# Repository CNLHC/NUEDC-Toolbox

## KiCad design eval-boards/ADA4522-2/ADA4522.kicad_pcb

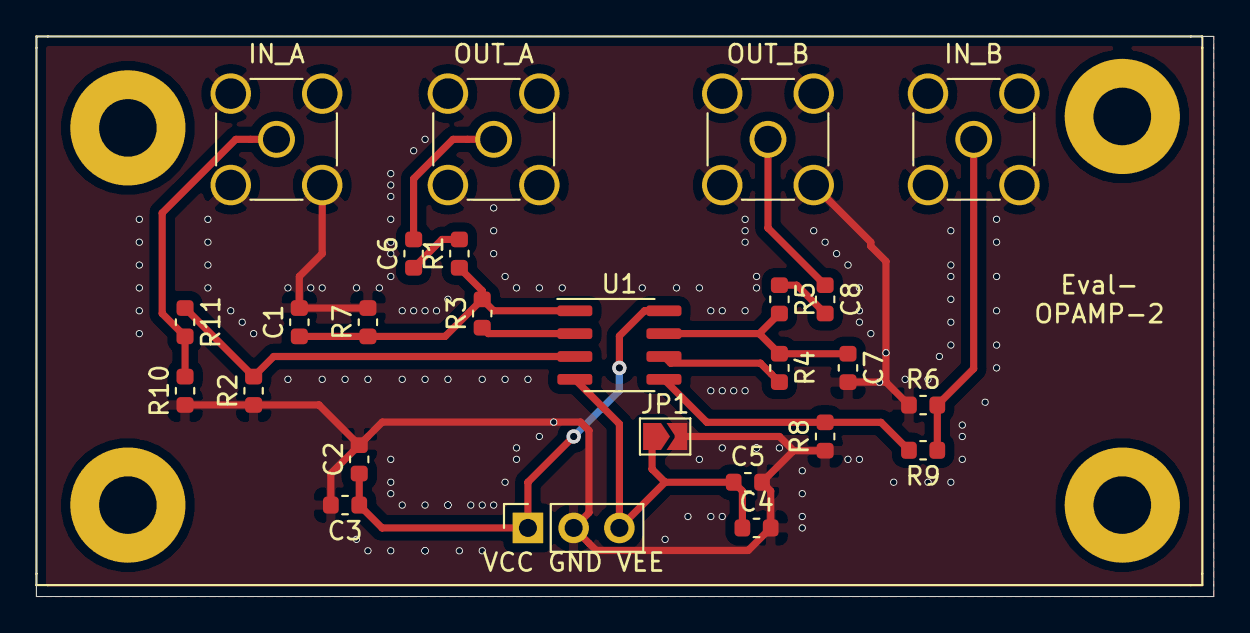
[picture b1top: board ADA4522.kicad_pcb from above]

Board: 2 copper layers, 65.4 x 31.1 mm, 26 parts (0 on the bottom side), 15 nets.

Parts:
C1, C6, C7, C8: 100pF; C_0603_1608Metric
C2, C4: 10uf; C_0603_1608Metric
C3, C5: 0.1uf; C_0603_1608Metric
IN_A: IN_A; SMA_Amphenol_132134-11_Vertical
IN_B: IN_B; SMA_Amphenol_132134-11_Vertical
JP1: SolderJumper-2_P1.3mm_Open_TrianglePad1.0x1.5mm
OUT_A: OUT_A; SMA_Amphenol_132134-11_Vertical
OUT_B: OUT_B; SMA_Amphenol_132134-11_Vertical
R1, R2, R3, R4, R5, R6, R7, R8, R9, R10, R11: R; R_0603_1608Metric
U1: ADA4522-2; SOIC-8_3.9x4.9mm_P1.27mm
VCC GND VEE: Conn_01x03_Male; PinSocket_1x03_P2.54mm_Vertical

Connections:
GND: C1.2, C2.2, C3.2, C4.2, C5.2, C7.2, IN_A.2, IN_B.2, JP1.2, OUT_A.2, OUT_B.2, R2.1, R6.1, R7.2, R8.1, R10.1, VCC GND VEE.2
unnamed: C1.1, R1.1, R3.2, R7.1, U1.1
unnamed: C2.1, C3.1, U1.8, VCC GND VEE.1
unnamed: C4.1, C5.1, JP1.1, U1.4, VCC GND VEE.3
unnamed: C6.1, R1.2
unnamed: C6.2, OUT_A.1
unnamed: C7.1, R4.1, R5.2, U1.7
unnamed: C8.1, OUT_B.1
unnamed: C8.2, R5.1
unnamed: IN_A.1, R10.2, R11.2
unnamed: IN_B.1, R6.2, R9.1
unnamed: R3.1, U1.2
unnamed: R4.2, U1.6
unnamed: R8.2, R9.2, U1.5
unnamed: R2.2, R11.1, U1.3

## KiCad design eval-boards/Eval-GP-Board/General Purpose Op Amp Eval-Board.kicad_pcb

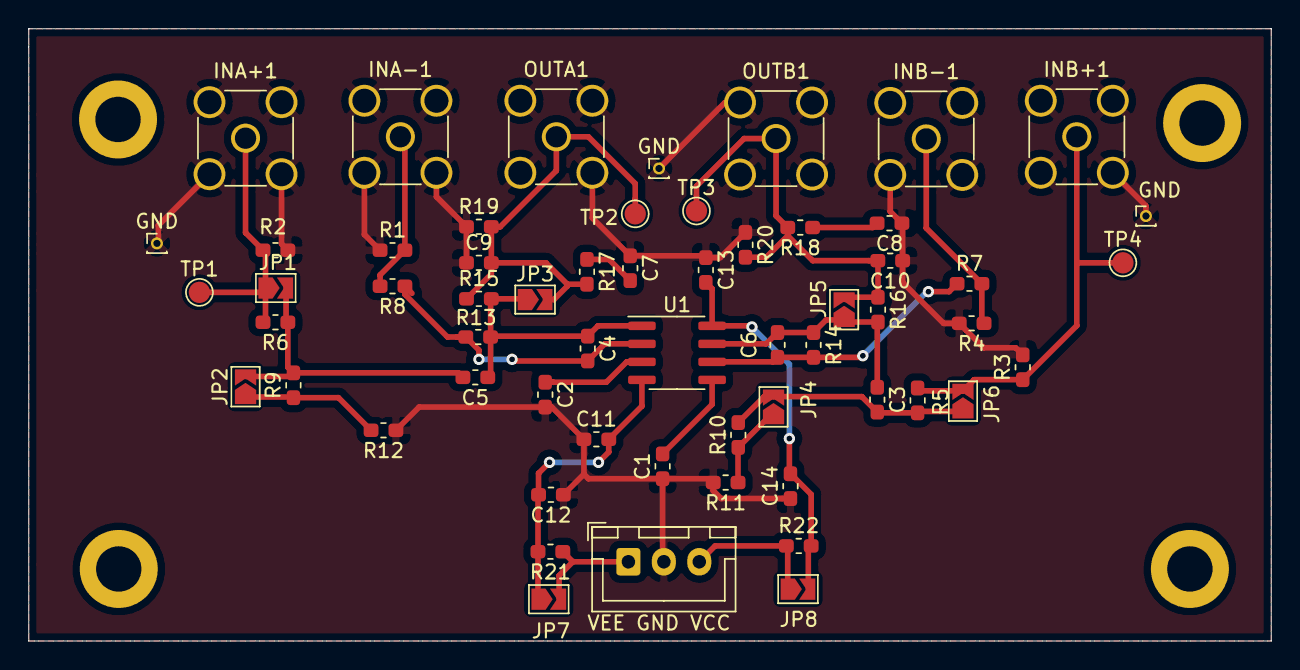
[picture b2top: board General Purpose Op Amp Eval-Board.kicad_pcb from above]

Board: 2 copper layers, 87.6 x 43.2 mm, 59 parts (0 on the bottom side), 23 nets.

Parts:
C1, C2, C3, C4, C5, C6, C7, C8, C9, C10, C11, C12, C13, C14: C; C_0603_1608Metric_Pad1.05x0.95mm_HandSolder
GND: PinHeader_1x01_P1.00mm_Vertical
GND#2, GND#3: PinHeader_1x01_P1.00mm_Vertical
INA+1: Conn_Coaxial; SMA_Amphenol_132134-11_Vertical
INA-1: Conn_Coaxial; SMA_Amphenol_132134-11_Vertical
INB+1: Conn_Coaxial; SMA_Amphenol_132134-11_Vertical
INB-1: Conn_Coaxial; SMA_Amphenol_132134-11_Vertical
JP1, JP2, JP3, JP4, JP5, JP6, JP7, JP8: SolderJumper-2_P1.3mm_Open_TrianglePad1.0x1.5mm
OUTA1: Conn_Coaxial; SMA_Amphenol_132134-11_Vertical
OUTB1: Conn_Coaxial; SMA_Amphenol_132134-11_Vertical
R1, R2, R3, R4, R5, R6, R7, R8, R9, R10, R11, R12, R13, R14, R15, R16, R17, R18, R19, R20, R21, R22: R; R_0603_1608Metric_Pad1.05x0.95mm_HandSolder
TP1, TP2, TP3, TP4: TestPoint_Pad_D1.5mm
U1: ADA4075-2; SOIC-8_3.9x4.9mm_P1.27mm
VEE GND VCC: Conn_01x03_Male; JST_XH_B3B-XH-A_1x03_P2.50mm_Vertical

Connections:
/VCC: JP8.1, R22.1, VEE GND VCC.3
/VEE: JP7.2, R21.1, VEE GND VCC.1
GND: C1.1, C2.2, C7.1, C8.1, C9.1, C10.1, C11.1, C12.1, C13.1, C14.1, GND.1, GND#2.1, GND#3.1, INA+1.2, INA-1.2, INB+1.2, INB-1.2, OUTA1.2, OUTB1.2, R1.1, R2.1, R3.2, R4.2, R11.2, R12.1, R19.1, R20.1, VEE GND VCC.2
unnamed: C1.2, U1.5
unnamed: C2.1, U1.3
unnamed: C3.1, C6.1, JP5.1, R14.1, R16.2, U1.7
unnamed: C3.2, JP4.2, JP6.1, R5.1, R10.2
unnamed: C4.1, C5.1, JP3.1, R13.1, R15.2, U1.1
unnamed: C4.2, R8.1, R13.2, U1.2
unnamed: C5.2, JP1.2, JP2.2, R6.1, R9.2
unnamed: C6.2, R7.1, R14.2, U1.6
unnamed: C7.2, R17.1
unnamed: C8.2, R18.1
unnamed: C9.2, JP3.2, OUTA1.1, R15.1, R17.2, R19.2, TP2.1
unnamed: C10.2, JP5.2, OUTB1.1, R16.1, R18.2, R20.2, TP3.1
unnamed: C11.2, C12.2, JP7.1, R21.2, U1.4
unnamed: C13.2, C14.2, JP8.2, R22.2, U1.8
unnamed: INA+1.1, JP1.1, R2.2, R6.2, TP1.1
unnamed: INA-1.1, R1.2, R8.2
unnamed: INB+1.1, JP6.2, R3.1, R5.2, TP4.1
unnamed: INB-1.1, R4.1, R7.2
unnamed: JP4.1, R10.1, R11.1
unnamed: JP2.1, R9.1, R12.2

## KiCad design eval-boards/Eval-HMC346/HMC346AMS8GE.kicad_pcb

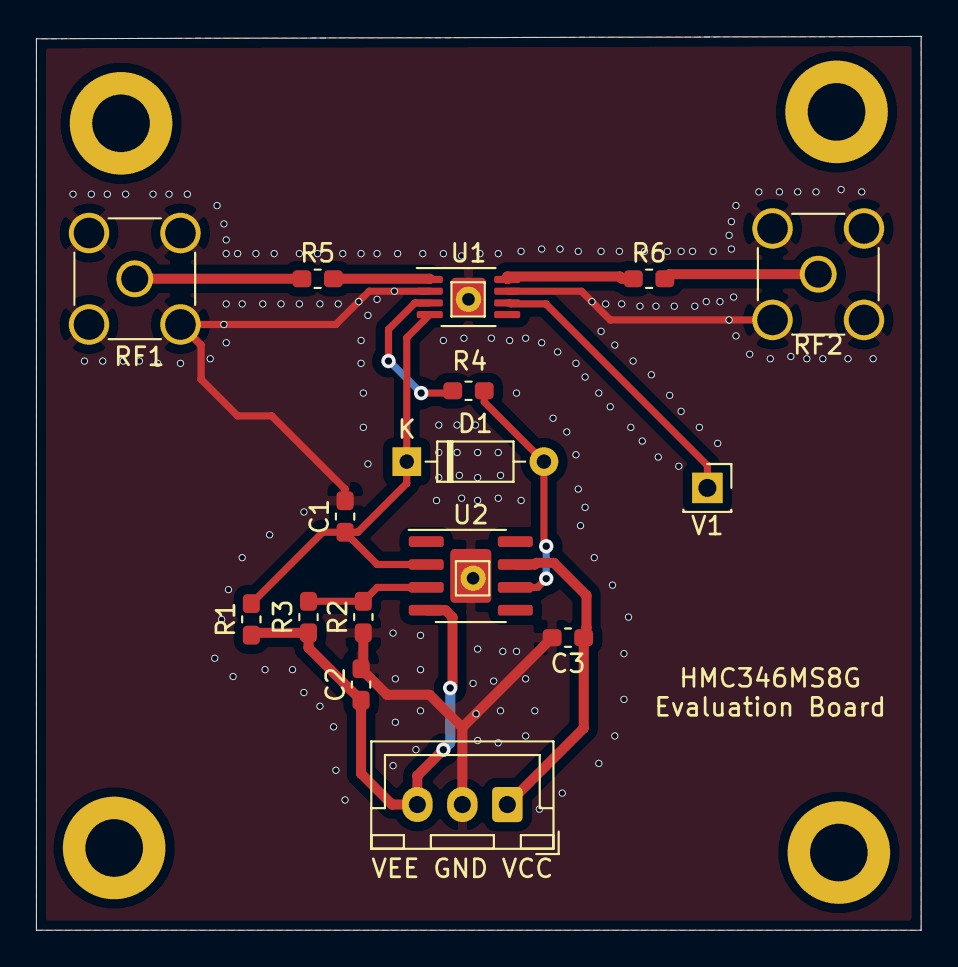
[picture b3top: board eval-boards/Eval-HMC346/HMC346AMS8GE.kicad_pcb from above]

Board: 2 copper layers, 49.1 x 49.7 mm, 16 parts (0 on the bottom side), 12 nets.

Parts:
C1, C2, C3: C; C_0603_1608Metric_Pad1.05x0.95mm_HandSolder
D1: 1N4148; D_DO-35_SOD27_P7.62mm_Horizontal
R1, R3: 3.92k; R_0603_1608Metric_Pad1.05x0.95mm_HandSolder
R2: 500; R_0603_1608Metric_Pad1.05x0.95mm_HandSolder
R4, R5, R6: R; R_0603_1608Metric_Pad1.05x0.95mm_HandSolder
RF1, RF2: Conn_Coaxial; SMA_Amphenol_901-144_Vertical
U1: HMC346AMS8GE; MSOP-8-1EP_3x3mm_P0.65mm_EP1.95x2.15mm
U2: THS4631D; SOIC-8-1EP_3.9x4.9mm_P1.27mm_EP2.29x3mm
V1: Conn_01x01_Male; PinSocket_1x01_P2.54mm_Vertical
VEE GND VCC: Conn_01x03_Male; JST_XH_B3B-XH-A_1x03_P2.50mm_Vertical

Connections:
/I: C1.1, D1.1, R1.2, U1.4, U2.2
/V1: U1.6, V1.1
/V2: R4.2, U1.3
/VCC: C3.1, U2.7, VEE GND VCC.1
/VEE: C2.1, R1.1, R3.1, U2.4, VEE GND VCC.3
GND: C1.2, C2.2, C3.2, R2.1, RF1.2, RF2.2, U1.2, U1.7, U1.9, U2.9, VEE GND VCC.2
unnamed: D1.2, R4.1, U2.6
unnamed: R5.1, RF1.1
unnamed: R6.2, RF2.1
unnamed: R2.2, R3.2, U2.3
unnamed: R5.2, U1.1
unnamed: R6.1, U1.8

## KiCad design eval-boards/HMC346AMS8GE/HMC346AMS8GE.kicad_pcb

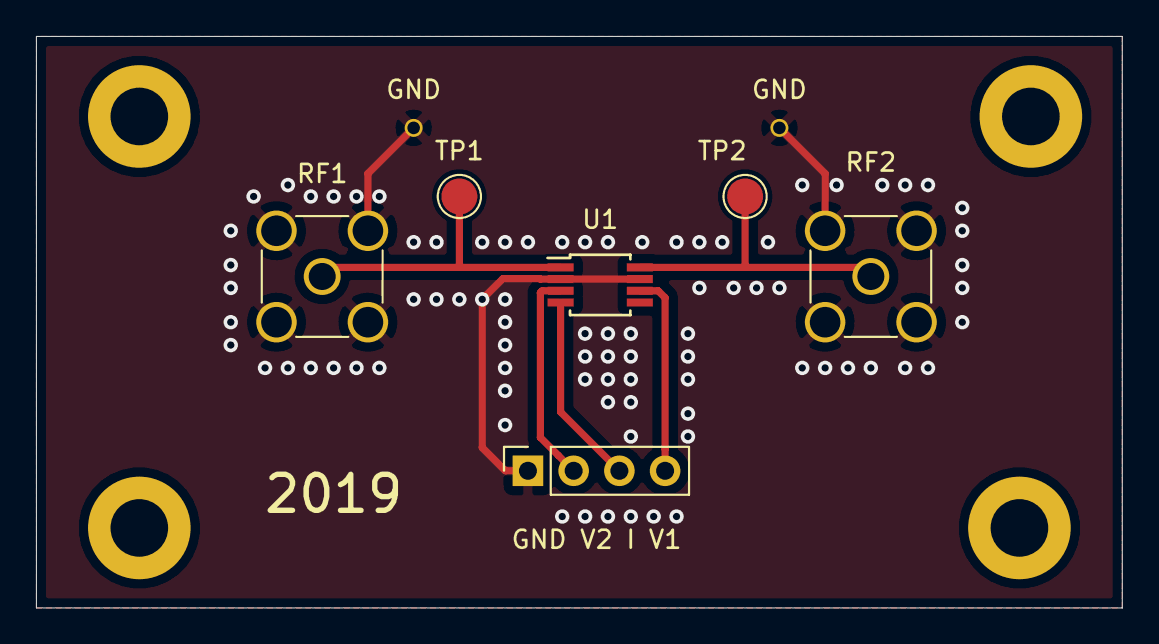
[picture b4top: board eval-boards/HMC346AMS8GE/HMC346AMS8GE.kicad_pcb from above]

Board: 2 copper layers, 60.3 x 31.8 mm, 8 parts (0 on the bottom side), 6 nets.

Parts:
GND: PinSocket_1x01_P1.27mm_Vertical
GND V2 I V1: Conn_01x04_Male; PinSocket_1x04_P2.54mm_Vertical
GND#2: PinSocket_1x01_P1.27mm_Vertical
RF1, RF2: Conn_Coaxial; SMA_Amphenol_901-144_Vertical
TP1, TP2: TestPoint_Pad_D2.0mm
U1: HMC346AMS8GE; MSOP-8_3x3mm_P0.65mm

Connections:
GND: GND.1, GND V2 I V1.1, GND#2.1, RF1.2, RF2.2, U1.2, U1.7
unnamed: RF1.1, TP1.1, U1.1
unnamed: RF2.1, TP2.1, U1.8
unnamed: GND V2 I V1.2, U1.3
unnamed: GND V2 I V1.3, U1.4
unnamed: GND V2 I V1.4, U1.6

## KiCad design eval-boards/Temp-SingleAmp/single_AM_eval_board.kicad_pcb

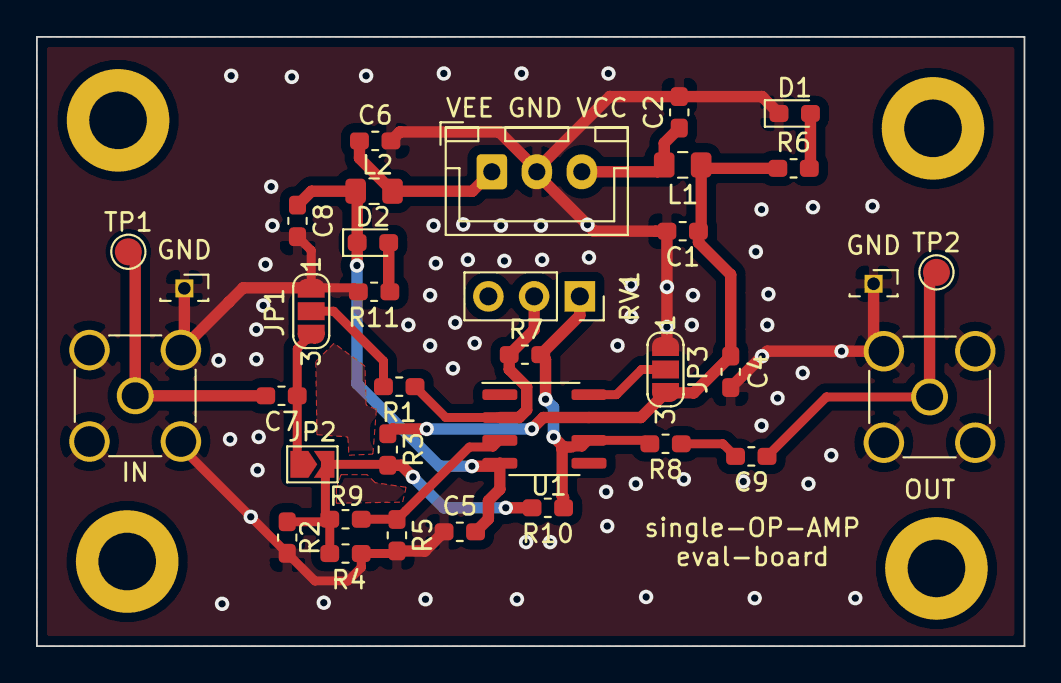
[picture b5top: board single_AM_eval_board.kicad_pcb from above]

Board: 2 copper layers, 54.9 x 33.8 mm, 35 parts (0 on the bottom side), 17 nets.

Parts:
C1, C2, C6, C8: 10uF; C_0603_1608Metric_Pad1.05x0.95mm_HandSolder
C4, C5: 100nF; C_0603_1608Metric_Pad1.05x0.95mm_HandSolder
C7, C9: C; C_0603_1608Metric_Pad1.05x0.95mm_HandSolder
D1, D2: LED_ALT; LED_0603_1608Metric_Pad1.05x0.95mm_HandSolder
GND: PinSocket_1x01_P1.27mm_Vertical
GND#2: PinSocket_1x01_P1.27mm_Vertical
IN: Conn_Coaxial; SMA_Amphenol_132134-11_Vertical
JP1, JP3: Jumper_3_Open; SolderJumper-3_P1.3mm_Open_RoundedPad1.0x1.5mm_NumberLabels
JP2: Jumper_2_Open; SolderJumper-2_P1.3mm_Open_TrianglePad1.0x1.5mm
L1, L2: L_Core_Iron; L_0805_2012Metric_Pad1.15x1.40mm_HandSolder
OUT: Conn_Coaxial; SMA_Amphenol_132134-11_Vertical
R1, R2, R3, R4, R5, R7, R8, R9, R10: R; R_0603_1608Metric_Pad1.05x0.95mm_HandSolder
R6, R11: 1K; R_0603_1608Metric_Pad1.05x0.95mm_HandSolder
RV1: R_POT; PinSocket_1x03_P2.54mm_Vertical
TP1, TP2: TestPoint_Pad_D1.5mm
U1: ADA4522-1; SOIC-8_3.9x4.9mm_P1.27mm
VEE GND VCC: Conn_01x03_Male; JST_XH_B3B-XH-A_1x03_P2.50mm_Vertical

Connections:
/VCC: C1.1, C4.2, JP3.3, L1.1, R3.1, R6.1, U1.7
/VEE: C5.2, C8.1, D2.1, L2.2, U1.4
GND: C1.2, C2.2, C4.1, C5.1, C6.2, C8.2, D1.1, GND.1, GND#2.1, IN.2, JP1.1, JP3.1, OUT.2, R2.2, R4.2, R5.2, R11.2, VEE GND VCC.2
unnamed: C2.1, L1.2, VEE GND VCC.3
unnamed: C6.1, L2.1, VEE GND VCC.1
unnamed: C7.1, JP1.3, JP2.1
unnamed: C7.2, IN.1, TP1.1
unnamed: C9.1, OUT.1, TP2.1
unnamed: C9.2, R8.1
unnamed: D1.2, R6.2
unnamed: D2.2, R11.1
unnamed: JP1.2, R1.2
unnamed: JP2.2, R2.1, R3.2, R4.1, R9.2, R10.2
unnamed: JP3.2, U1.8
unnamed: R1.1, R7.2, RV1.2, U1.2
unnamed: R5.1, R9.1, U1.3
unnamed: R7.1, R8.2, R10.1, RV1.1, U1.6

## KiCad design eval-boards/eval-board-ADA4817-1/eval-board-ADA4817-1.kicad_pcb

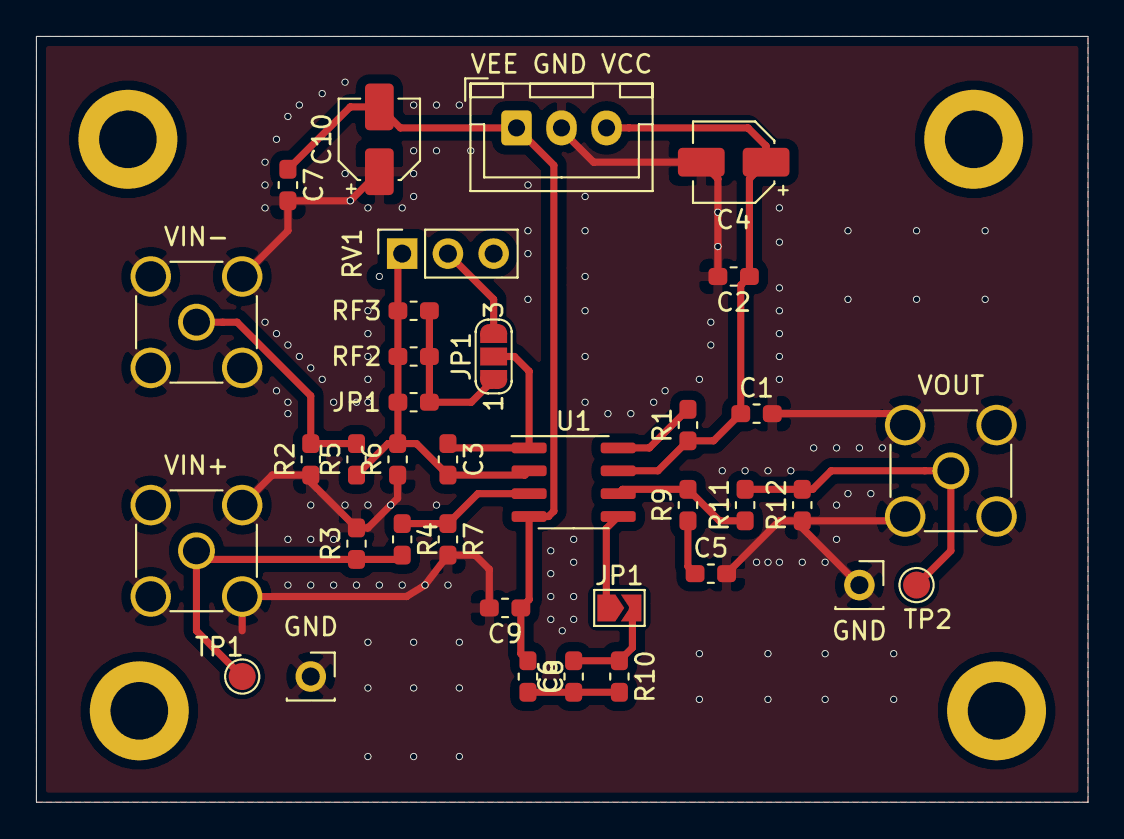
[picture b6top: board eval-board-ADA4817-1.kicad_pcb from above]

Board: 2 copper layers, 58.4 x 42.5 mm, 36 parts (0 on the bottom side), 16 nets.

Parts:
C1, C2, C7, C9: 0.1uF; C_0603_1608Metric_Pad1.05x0.95mm_HandSolder
C3: CF; C_0603_1608Metric_Pad1.05x0.95mm_HandSolder
C4, C10: 10uF; CP_Elec_4x5.4
C5: CL; C_0603_1608Metric_Pad1.05x0.95mm_HandSolder
C6, C8: C; C_0603_1608Metric_Pad1.05x0.95mm_HandSolder
GND: PinSocket_1x01_P2.54mm_Vertical
GND#2: PinSocket_1x01_P2.54mm_Vertical
JP1: SolderJumper-2_P1.3mm_Open_TrianglePad1.0x1.5mm
JP1#2: Jumper_3_Open; SolderJumper-3_P1.3mm_Open_RoundedPad1.0x1.5mm_NumberLabels
JP1#3: R; R_0603_1608Metric_Pad1.05x0.95mm_HandSolder
R1: 1kΩ; R_0603_1608Metric_Pad1.05x0.95mm_HandSolder
R2: RTN; R_0603_1608Metric_Pad1.05x0.95mm_HandSolder
R3: RTP; R_0603_1608Metric_Pad1.05x0.95mm_HandSolder
R4, R5, R6, R7, R10, R11, R12: R; R_0603_1608Metric_Pad1.05x0.95mm_HandSolder
R9: RS; R_0603_1608Metric_Pad1.05x0.95mm_HandSolder
RF2, RF3: R; R_0603_1608Metric_Pad1.05x0.95mm_HandSolder
RV1: R_POT; PinSocket_1x03_P2.54mm_Vertical
TP1, TP2: TestPoint_Pad_D1.5mm
U1: ADA4817-1; SOIC-8_3.9x4.9mm_P1.27mm
VEE GND VCC: Conn_01x03_Male; JST_XH_B3B-XH-A_1x03_P2.50mm_Vertical
VIN+: +VIN; SMA_Amphenol_132134-11_Vertical
VIN-: -VIN; SMA_Amphenol_132134-11_Vertical
VOUT: VOUT; SMA_Amphenol_132134-11_Vertical

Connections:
/PD: R1.2, U1.8
/VCC: C1.1, C2.1, C4.1, R1.1, U1.7, VEE GND VCC.3
/VEE: C7.1, C8.1, C9.1, C10.2, U1.4, VEE GND VCC.1
GNDREF: C1.2, C2.2, C4.2, C5.2, C7.2, C9.2, C10.1, GND.1, GND#2.1, R2.1, R3.2, R6.1, R7.2, R12.1, VEE GND VCC.2, VIN+.2, VIN-.2, VOUT.2
unnamed: C3.1, JP1#2.2, U1.1
unnamed: C3.2, JP1#3.1, R5.1, R6.2, RF2.1, RF3.2, RV1.1, U1.2
unnamed: C5.1, R9.1
unnamed: C6.1, C8.2, R10.2
unnamed: C6.2, JP1.1, JP1.2, R10.1, U1.5
unnamed: R2.2, R5.2, VIN-.1
unnamed: R3.1, R4.2, TP1.1, VIN+.1
unnamed: R11.2, R12.2, TP2.1, VOUT.1
unnamed: JP1#2.1, JP1#3.2, RF2.2, RF3.1
unnamed: JP1#2.3, RV1.2
unnamed: R4.1, R7.1, U1.3
unnamed: R9.2, R11.1, U1.6
